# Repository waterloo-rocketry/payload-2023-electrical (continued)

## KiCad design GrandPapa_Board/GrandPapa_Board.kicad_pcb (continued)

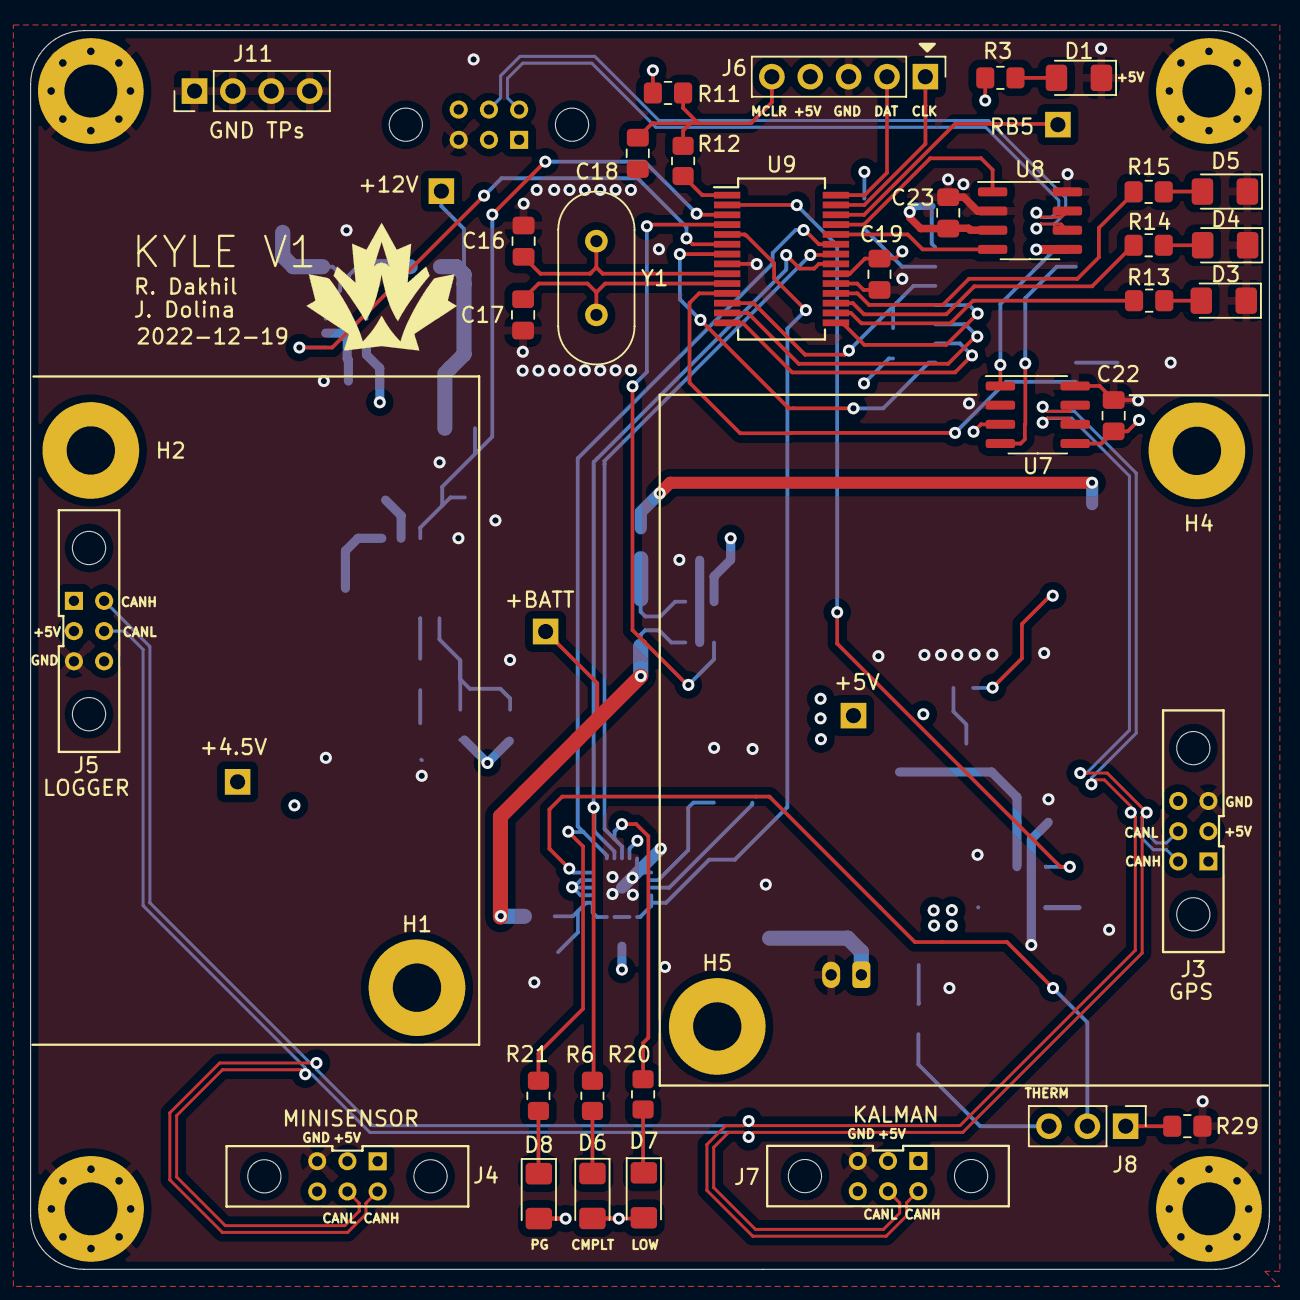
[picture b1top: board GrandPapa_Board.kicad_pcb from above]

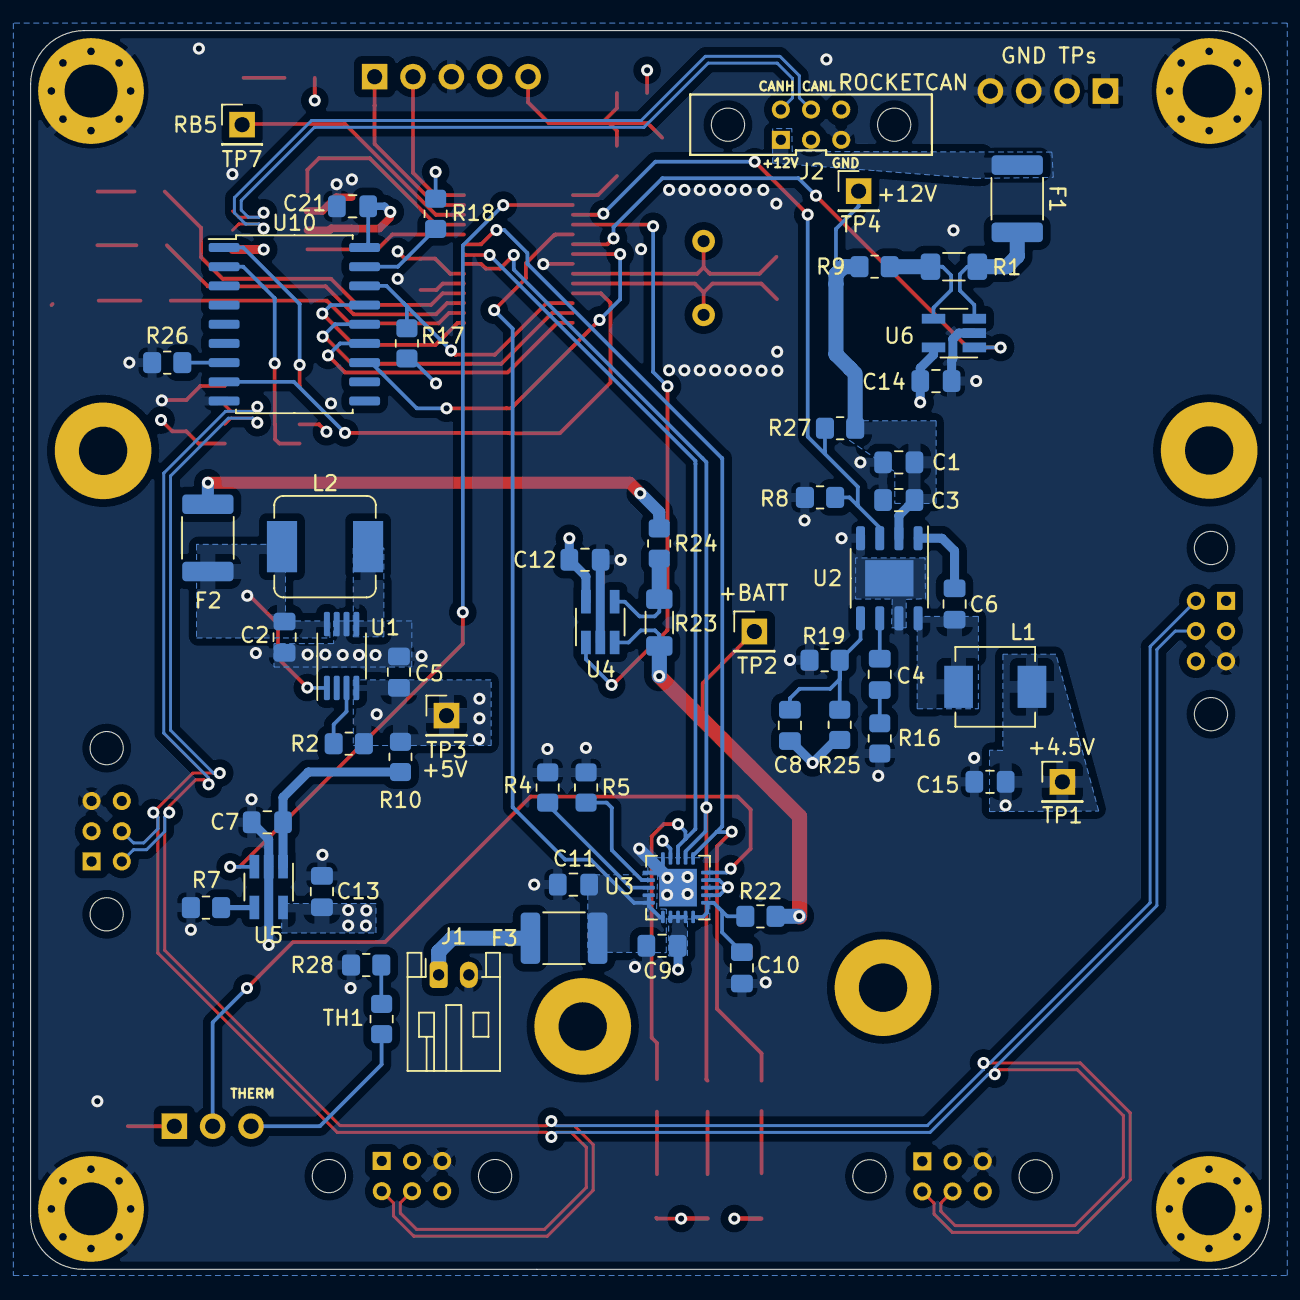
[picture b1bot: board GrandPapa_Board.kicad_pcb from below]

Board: 4 copper layers, 82.0 x 82.0 mm, 97 parts (55 on the bottom side), 70 nets.

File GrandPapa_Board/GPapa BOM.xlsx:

Column1 | Column2 | Column3 | Column4 | Column5 | Column6 | Column7
Source: | C:\Users\joedo\Documents\UW Rocketry\payload-2023-electrical\GrandPapa_Board\Gr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
Date: | 2022-12-09 12:44:19 PM
Tool: | Eeschema (6.0.5)
Generator: | C:\Program Files\KiCad\6.0\bin\scripting\plugins/bom_csv_grouped_by_value_with_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
Component Count: | 94
Ref | Qnty | Value | Cmp name | Footprint | Description | In Stock In Bay
C1, C2, C5, C22, C23, | 5 | 10uF | C_Small | Capacitor_SMD:C_0805_2012Metric_Pad1.18x1.45mm_HandSolder | Unpolarized capacitor, small symbol | 43 in the bay
C3, C6, C12, C13, C14, C21, | 6 | 0.1uF | C_Small | Capacitor_SMD:C_0805_2012Metric_Pad1.18x1.45mm_HandSolder | Unpolarized capacitor, small symbol | 100+ in the bay
C4, | 1 | 5nF | C_Small | Capacitor_SMD:C_0805_2012Metric_Pad1.18x1.45mm_HandSolder | Unpolarized capacitor, small symbol | 0
C7, C9, C10, C11, | 4 | 4.7uF | C | Capacitor_SMD:C_0805_2012Metric_Pad1.18x1.45mm_HandSolder | Unpolarized capacitor | 50~ in the Bay
C8, | 1 | 25pF | C_Small | Capacitor_SMD:C_0805_2012Metric_Pad1.18x1.45mm_HandSolder | Unpolarized capacitor, small symbol | 25 in the Bay
C15, | 1 | 44 uF | C_Small | Capacitor_SMD:C_0805_2012Metric_Pad1.18x1.45mm_HandSolder | Unpolarized capacitor, small symbol | 0
C16, C17, | 2 | 27pF | C_Small | Capacitor_SMD:C_0805_2012Metric_Pad1.18x1.45mm_HandSolder | Unpolarized capacitor, small symbol | 100+ in the Bay
C18, C19, | 2 | 0.1uF 20V | C_Small | Capacitor_SMD:C_0805_2012Metric_Pad1.18x1.45mm_HandSolder | Unpolarized capacitor, small symbol | 49 in the bay
D1, D5, D8, | 3 | 150120BS75000 | LED | LED_SMD:LED_1206_3216Metric_Pad1.42x1.75mm_HandSolder | Light emitting diode | 100+ in bay
D3, D6, | 2 | QBLP650-IW | LED | LED_SMD:LED_1206_3216Metric_Pad1.42x1.75mm_HandSolder | Light emitting diode | 100+ in bay
D4, D7, | 2 | 156120RS75000 | LED | LED_SMD:LED_1206_3216Metric_Pad1.42x1.75mm_HandSolder | Light emitting diode | 100+ in bay
F1, F3, | 2 | 1.5A | Polyfuse | Fuse:Fuse_0805_2012Metric_Pad1.15x1.40mm_HandSolder | Resettable fuse, polymeric positive temperature coefficient
F2, | 1 | 1.2A | Polyfuse | Fuse:Fuse_0805_2012Metric_Pad1.15x1.40mm_HandSolder | Resettable fuse, polymeric positive temperature coefficient
H1, H2, H3, H4, H5, H6, H7, H8, | 8 | MountingHole_Pad | MountingHole_Pad | MountingHole:MountingHole_3.5mm_Pad_Via | Mounting Hole with connection | N/A
J1, | 1 | 3.7V LiPo Single Cell | Conn_01x02_Female | Connector_JST:JST_PH_S2B-PH-K_1x02_P2.00mm_Horizontal | Generic connector, single row, 01x02, script generated (kicad-library-utils/sch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
J2, | 1 | HARWIN_ROCKET | Conn_01x05 | PapaOld:connector_Harwin_M80-5000642 | Generic connector, single row, 01x05, script generated (kicad-library-utils/sch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 | N/A
J3, | 1 | Dupont_GPS | Conn_01x06_Female | PapaOld:connector_Harwin_M80-5000642 | Generic connector, single row, 01x06, script generated (kicad-library-utils/sch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
J4, | 1 | HARWIN_MINISENSOR | Conn_01x05 | PapaOld:connector_Harwin_M80-5000642 | Generic connector, single row, 01x05, script generated (kicad-library-utils/sch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 | N/A
J5, | 1 | Dupont_Logger | Conn_01x06_Female | PapaOld:connector_Harwin_M80-5000642 | Generic connector, single row, 01x06, script generated (kicad-library-utils/sch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
J6, | 1 | Prog Header | Conn_01x05_Female | Connector_PinHeader_2.54mm:PinHeader_1x05_P2.54mm_Vertical | Generic connector, single row, 01x05, script generated (kicad-library-utils/sch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
J7, | 1 | HARWIN_KALMAN | Conn_01x05 | PapaOld:connector_Harwin_M80-5000642 | Generic connector, single row, 01x05, script generated (kicad-library-utils/sch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 | N/A
J11, | 1 | Dupont 01x04_Male | Conn_01x04_Male | Connector_PinHeader_2.54mm:PinHeader_1x04_P2.54mm_Vertical | Generic connector, single row, 01x04, script generated (kicad-library-utils/sch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
L1, | 1 | 5.6uH | L | Inductor_SMD:L_Vishay_IHLP-2020 | Inductor | ORD
L2, | 1 | 4.7uH | L_Small | Inductor_SMD:L_Sumida_CDMC6D28_7.25x6.5mm | Inductor, small symbol | ORD
R1, R23, | 2 | 20mR | R_US | Resistor_SMD:R_1206_3216Metric_Pad1.30x1.75mm_HandSolder | Resistor, US symbol
R2, | 1 | 1MR | R_Small_US | Resistor_SMD:R_0805_2012Metric_Pad1.20x1.40mm_HandSolder | Resistor, small US symbol
R3, R12, R13, R15, | 4 | 100R | R_Small_US | Resistor_SMD:R_0805_2012Metric_Pad1.20x1.40mm_HandSolder | Resistor, small US symbol
R4, | 1 | 2kR | R_Small_US | Resistor_SMD:R_0805_2012Metric_Pad1.20x1.40mm_HandSolder | Resistor, small US symbol
R5, | 1 | 25kR | R_Small_US | Resistor_SMD:R_0805_2012Metric_Pad1.20x1.40mm_HandSolder | Resistor, small US symbol
R6, R20, R21, | 3 | 470R | R_Small_US | Resistor_SMD:R_0805_2012Metric_Pad1.20x1.40mm_HandSolder | Resistor, small US symbol
R7, | 1 | 500R | R_US | Resistor_SMD:R_0805_2012Metric_Pad1.20x1.40mm_HandSolder | Resistor, US symbol
R8, R11, R17, R18, R26, | 5 | 10kR | R_Small_US | Resistor_SMD:R_0805_2012Metric_Pad1.20x1.40mm_HandSolder | Resistor, small US symbol
R9, R10, R22, R24, | 4 | 0 | R_Small_US | Resistor_SMD:R_0805_2012Metric_Pad1.20x1.40mm_HandSolder | Resistor, small US symbol
R14, | 1 | 150R | R_Small_US | Resistor_SMD:R_0805_2012Metric_Pad1.20x1.40mm_HandSolder | Resistor, small US symbol
R16, | 1 | 11kR | R_Small_US | Resistor_SMD:R_0805_2012Metric_Pad1.20x1.40mm_HandSolder | Resistor, small US symbol
R19, | 1 | 70kR | R_Small_US | Resistor_SMD:R_0805_2012Metric_Pad1.20x1.40mm_HandSolder | Resistor, small US symbol
R25, | 1 | 324kR | R_Small_US | Resistor_SMD:R_0805_2012Metric_Pad1.20x1.40mm_HandSolder | Resistor, small US symbol
R27, | 1 | 15kR | R_US | Resistor_SMD:R_0805_2012Metric_Pad1.20x1.40mm_HandSolder | Resistor, US symbol
TH1, | 1 | 10k | Thermistor_NTC | Resistor_SMD:R_0805_2012Metric_Pad1.20x1.40mm_HandSolder | Temperature dependent resistor, negative temperature coefficient | ORD
TP1, TP2, TP3, TP4, TP7, | 5 | TestPoint | TestPoint | Connector_PinHeader_2.54mm:PinHeader_1x01_P2.54mm_Vertical | test point
U1, | 1 | MCP1642B-50I/MS | MCP1642B{slash}D-xx | Package_SO:MSOP-8_3x3mm_P0.65mm | Fixed Output Boost Regulator | ORD
U2, | 1 | BD9E302EFJ | BD9E302EFJ | Package_SO:HTSOP-8-1EP_3.9x4.9mm_P1.27mm_EP2.4x3.2mm |  | ORD
U3, | 1 | MCP73871T-1CCI/ML | MCP73871 | Package_DFN_QFN:QFN-20-1EP_4x4mm_P0.5mm_EP2.5x2.5mm | Single cell, Li-Ion/Li-Po charge management controller | ORD
U4, U6, | 2 | INA180 | INA180 | Package_TO_SOT_SMD:SOT-23-5_HandSoldering | Low- and High-Side Voltage Output, Current-Sense Amplifier
U5, | 1 | FPF2124 | FPF2124 | Package_TO_SOT_SMD:SOT-23-5_HandSoldering |  | ORD
U7, U8, | 2 | MCP2562-E/SN | MCP2562 | Package_SO:SOIC-8_3.9x4.9mm_P1.27mm | High-Speed CAN Transceiver
U9, | 1 | PIC18F26K83 | PIC18F26K83 | Package_SO:SSOP-28_5.3x10.2mm_P0.65mm | 28-Pin, Low-Power, High-Performance Microcontrollers with CAN Technology
U10, | 1 | MCP2515-I/P | MCP2515 | Package_SO:SOIC-18W_7.5x11.6mm_P1.27mm |  | ORD
Y1, | 1 | 12MHz | Crystal | Crystal:Crystal_HC49-4H_Vertical | Two pin crystal | IN STOCK

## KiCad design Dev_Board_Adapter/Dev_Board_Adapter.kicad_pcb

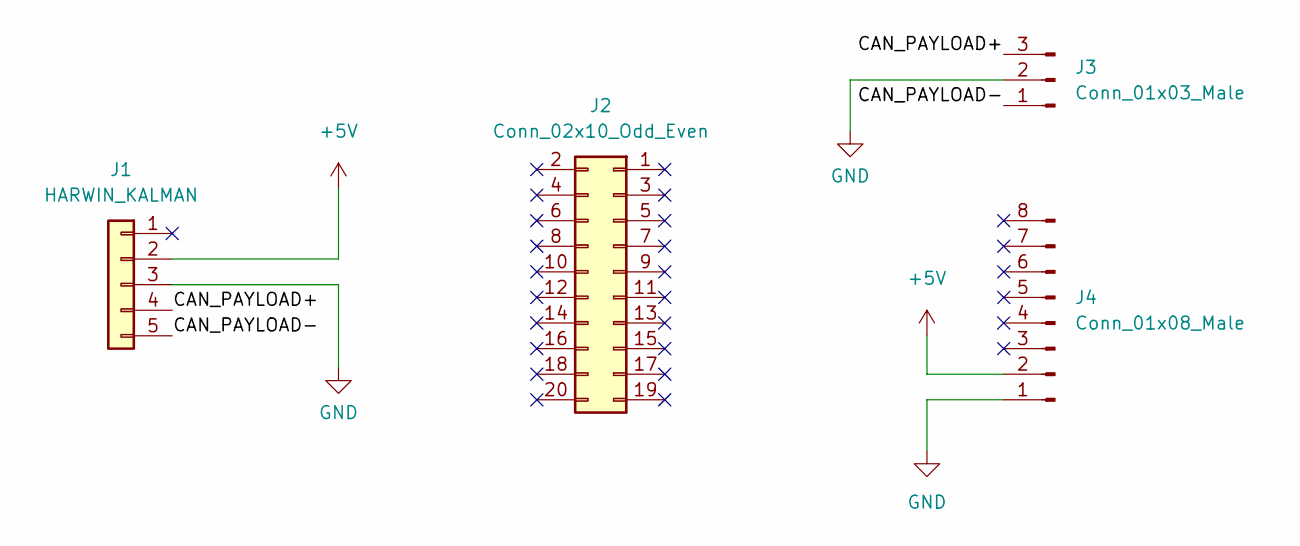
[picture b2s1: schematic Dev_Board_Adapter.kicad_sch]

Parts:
J1: HARWIN_KALMAN; connector_Harwin_M80-5000642
J2: Conn_02x10_Odd_Even; PinHeader_2x10_P2.54mm_Vertical
J3: Conn_01x03_Male; PinHeader_1x03_P2.54mm_Vertical
J4: Conn_01x08_Male; PinHeader_1x08_P2.54mm_Vertical

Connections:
+5V: J1.2, J4.2
/CAN_PAYLOAD+: J1.4, J3.3
/CAN_PAYLOAD-: J1.5, J3.1
GND: J1.3, J3.2, J4.1

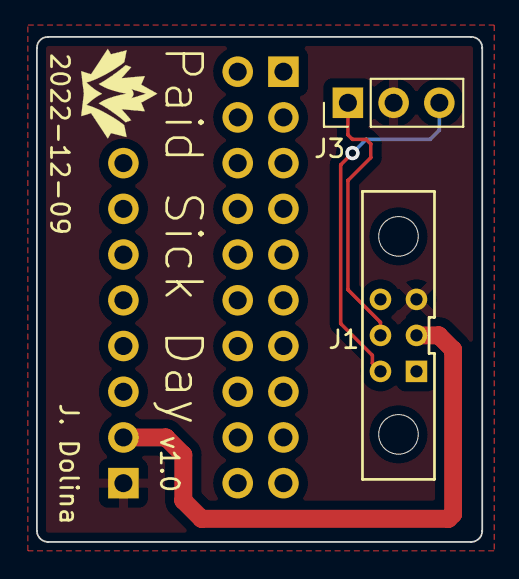
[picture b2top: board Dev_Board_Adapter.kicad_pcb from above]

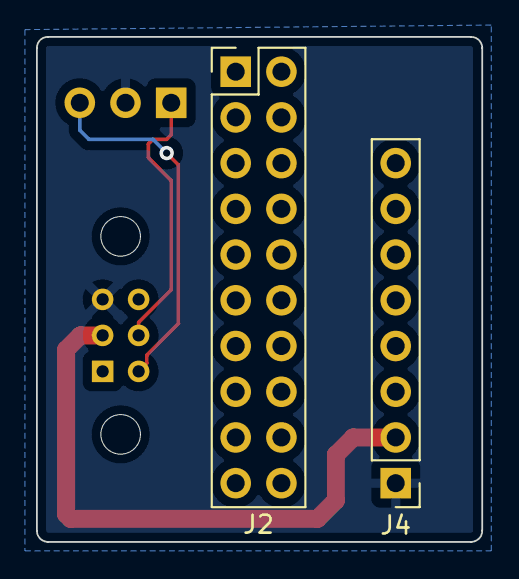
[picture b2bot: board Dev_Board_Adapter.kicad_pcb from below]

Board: 2 copper layers, 24.7 x 28.1 mm, 4 parts (2 on the bottom side), 4 nets.

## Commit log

2022-09-18 Add block diagram
2022-09-25 Update sys diagram
2022-09-25 Init Grandpapa project files, updated README
2022-09-25 Update digram
2022-09-26 Shameless papa copying pt 1
2022-09-27 Add power circuits and some PIC stuff, grandpapa lib
    5V buck, 3.3V LDO, load switches, current and voltage sensing, some PIC stuff
2022-09-27 Add missing capacitor value, annotate symbols
2022-09-27 Add motor current sense amp and board output connections
2022-09-27 Add MCP2515, MCU pin naming scheme
2022-09-28 Add INA180 to symbol lib, update 5v switch labels
2022-09-29 Add FETs to power lines
2022-09-30 clean up schematic, edit nets for clarification, add gnd test points, edit load switching scheme
2022-10-09 Remove 3.3V, placeholders for battery charge IC and 5V boost converter
2022-10-16 added MCP73871
2022-10-17 add 5V boost converter and 12V load switch, finish battery charge circuit
2022-10-17 add missing datasheets
2022-10-22 clean up schematic, fix some ERC errors
2022-10-26 move 12V shutoff to reg, rm motor stuff, subsheet/global pin redesign
2022-10-26 fix erc
2022-10-30 fix SHDN pin config on 4.5V regulator
2022-10-31 Addressed some Jack comments. 3/4/6/7 TBD
2022-11-03 address the rest of jack's review, still need to fix grid spacing
2022-11-06 fix disconnected pins, connect new hierarchical pins, misc layout changes
2022-11-07 minor fixes; chip shortage tearing me a new one
2022-11-10 added new buck reg IC, external component values TBA
2022-11-12 more buck conv component sizing
2022-11-12 component sizing for 4.5V buck complete
2022-11-13 Addded 5V boost and kalman board connector
2022-11-13 minor changes, change some buck converter component values, add inductor + LED part numbers
2022-11-16 fix 4.5V buck reg enable pin
2022-11-16 fix comments
2022-11-19 Add footprints, inductors TBD
2022-11-20 Finish footprints, add board outline
2022-11-20 add footprints, group layouts
2022-11-23 change stackup, mounting holes, connector footprints, power reg layout, fuse values
2022-12-03 add footprint library
2022-12-03 4 straight hours of traces
2022-12-07 update layout + routing
2022-12-07 Fix silkscreen; add logo
2022-12-08 Fix DRC errors
2022-12-08 undo errant schematic changes
2022-12-08 update README, 2nd attempt
2022-12-09 fix U8 pin 6 connection
2022-12-09 Add R28 to fix thermal shdn; Add BOM and thermistor calc sheets
2022-12-09 Create schematic; exact layout TBD
2022-12-09 Fix silkscreen
2022-12-10 fix spacing
2022-12-10 fix edge cuts
2022-12-10 Cleanup spacing, edges, corners
2022-12-10 Fix corners for real
2022-12-10 Add logo n stuff; front pour
2022-12-10 Generate gerbers
2022-12-10 fix gitignore, update BOM
2022-12-10 Add jumper to bypass thermal shutdown
2022-12-12 minor PCB changes, fix logger mounting hole placement, minor schematic cleanup
2022-12-12 fix battery LED indicator labels
2022-12-13 Address Jack's comments, minor schematic text cleanup
2022-12-13 missed F3, update PDF
2022-12-13 Generate STEP file
2022-12-15 Update BOM for ordering
2022-12-16 flip Harwin; regen gerbers; add PDF
2022-12-16 gerbers, take 2
2022-12-17 Move/rotate Harwins
2022-12-17 route CAN diff pairs, generate gerbers
2022-12-20 Fix ur gitignore
2022-12-20 Ew osx
2022-12-20 Finalize date on sikscreen; regen gerbers
2022-12-23 Remove local copy of canhw lib
2023-01-09 schematic of wiring for rogallo wing test setup
2023-02-01 swapped for arduino nano
2023-04-19 fix charging prog1 resistor value, fix schematic grid
